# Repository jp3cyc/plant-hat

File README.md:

# plant-hat
ラズパイで植物の水やりをするための基板

# 機能
  - 12V入力対応（ラズパイ用USB電源不要）
  - 12VモータPWM駆動回路搭載
  - I2C用コネクタ搭載
  - ユニバーサル基板エリアあり
  - 3cm角ファン搭載可能

# 使い方
## 電源ON
  DCジャックに12V電源を差し込み，スイッチをONにするとラズパイが起動します．（Rev1基板ではON-OFFの印刷が逆転しています）
  
## GPIO操作
  - J7コネクタはGPIO 35，J6コネクタは32番に接続されています．
  - GPIO35番をONにしたいときは，GPIO35の出力をHにしてください．
  - GPIO35，GPIO32はPWM出力に対応しているので，PWM出力が可能です（未検証）
  - ラズパイのGPIOを操作できればソフトウェアは何でも使えます（例：C，Python，Node-redなど）

## 利用上の注意
Raspberry Piの時計のタイマーは符号付き32bit intで実装されている都合上，2038年1月19日12時14分7秒(JST)を超えると，1901年にタイムスリップします．
そのため，2038年1月19日12時14分7秒をまたぐ水やりを行うと，プログラムの実装によっては水が出続ける可能性があります．
ご利用時はご注意ください．

https://ja.wikipedia.org/wiki/2038%E5%B9%B4%E5%95%8F%E9%A1%8C
https://www.youtube.com/watch?v=WLyIPslm_rw

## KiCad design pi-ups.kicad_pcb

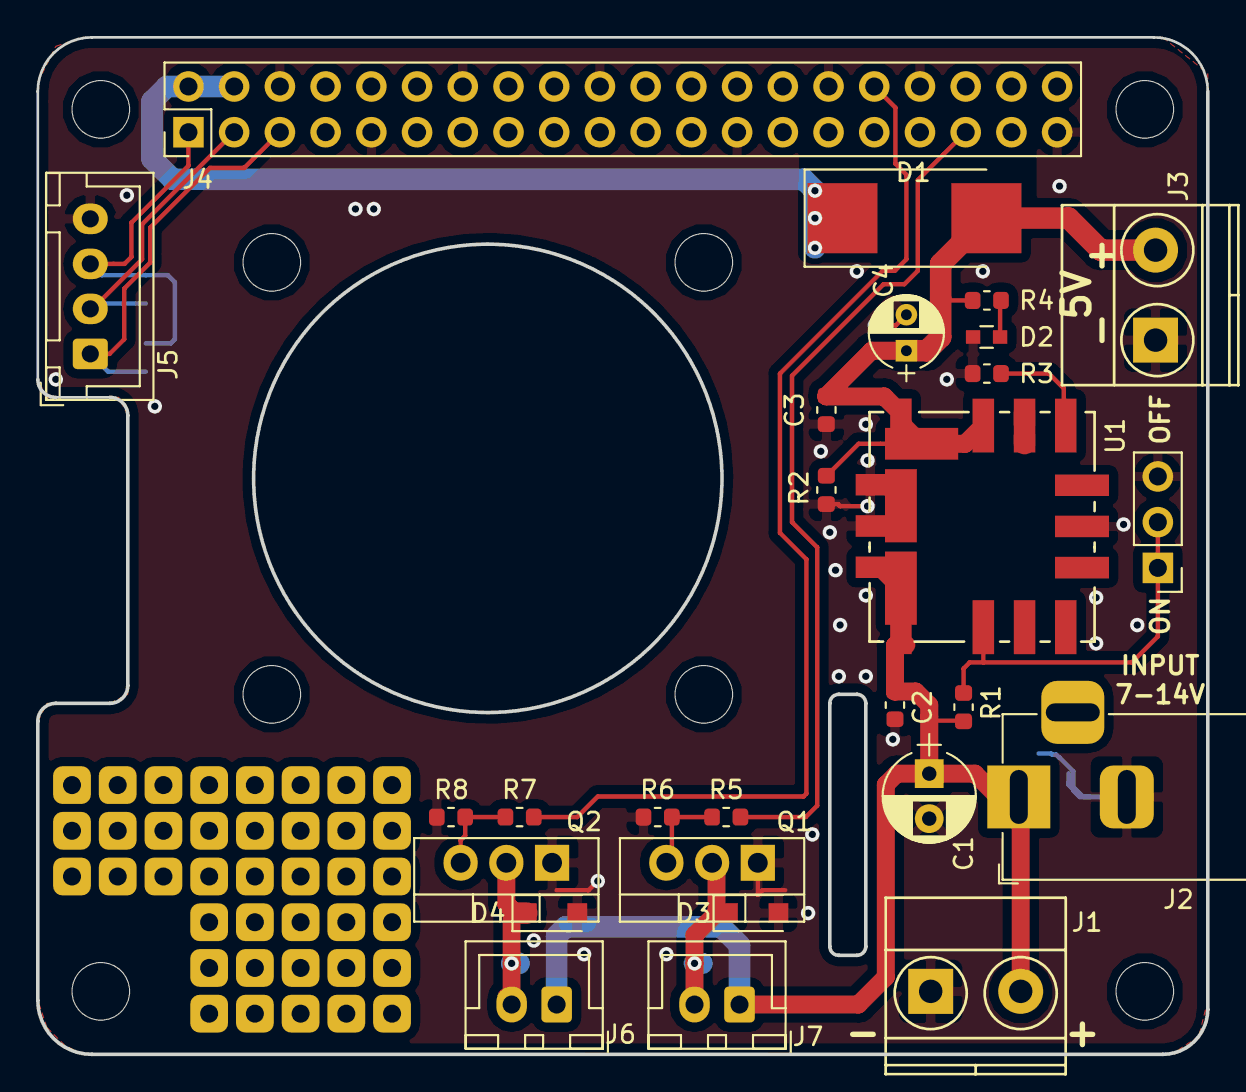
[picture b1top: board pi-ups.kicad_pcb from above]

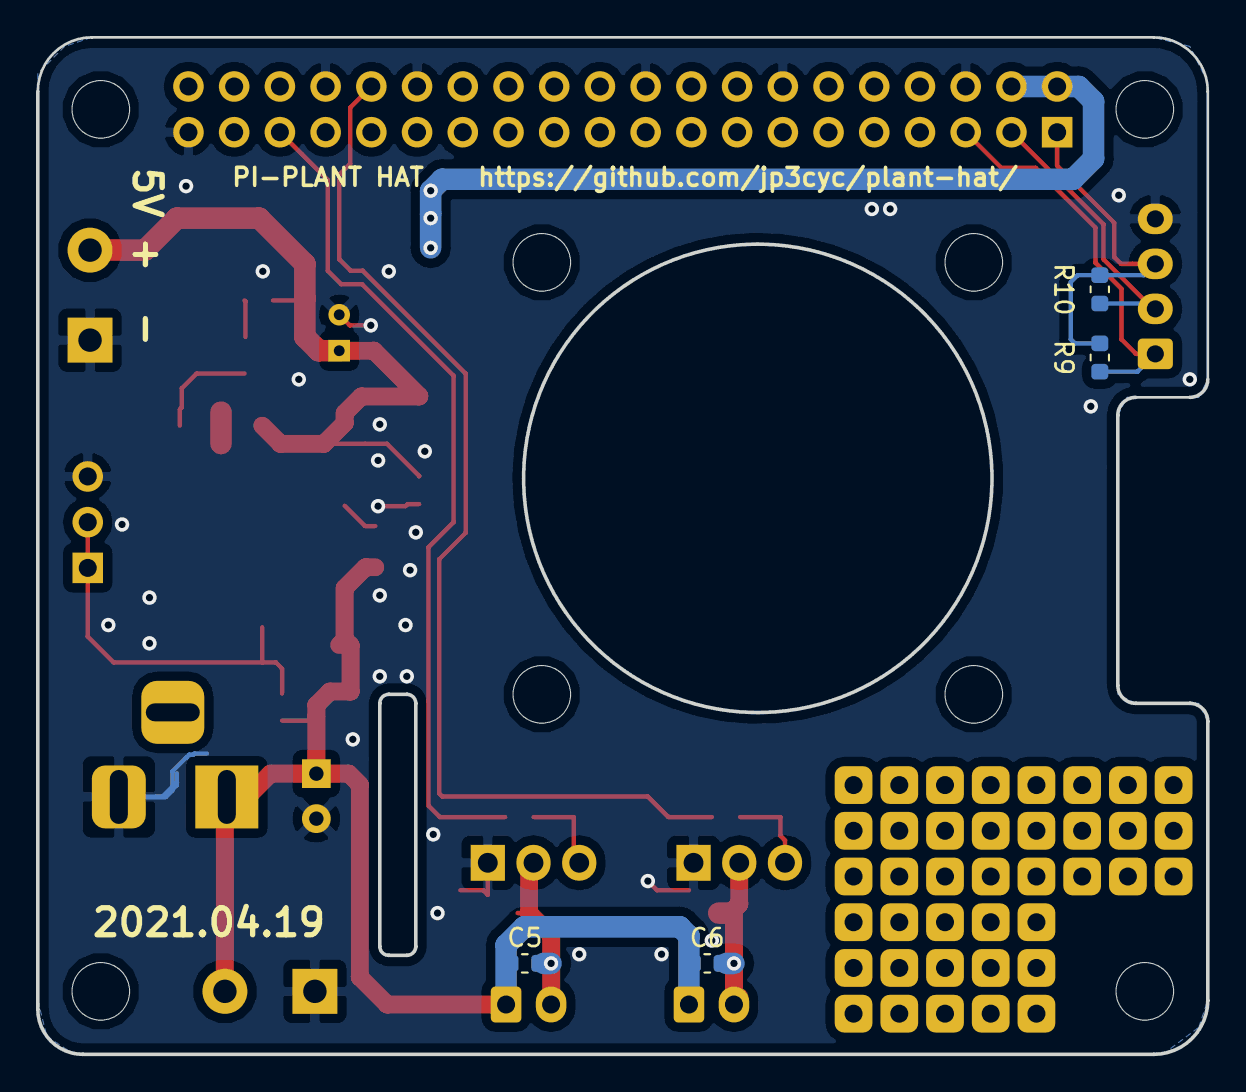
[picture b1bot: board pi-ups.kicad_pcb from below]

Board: 2 copper layers, 65.0 x 56.5 mm, 31 parts (4 on the bottom side), 16 nets.

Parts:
C1: 22u; CP_Radial_D5.0mm_P2.50mm
C2, C3, C5, C6: 0.1u; C_0603_1608Metric
C4: 10u; CP_Radial_D4.0mm_P2.00mm
D1: D; D_3220
D2: ON-LINE; C_0603
D3, D4: SS2040FL; D_SOD-123F
J1: Battery; TerminalBlock_Pheonix_MKDS1.5-2pol
J2: Jack-DC; BarrelJack_Horizontal
J3: 5V; TerminalBlock_Pheonix_MKDS1.5-2pol
J4: Raspi GPIO; Pin_Header_Straight_2x20_Pitch2.54mm
J5: I2C; JST_XH_B04B-XH-A_1x04_P2.50mm_Vertical
J6, J7: Motor; JST_XH_B02B-XH-A_1x02_P2.50mm_Vertical
Q1, Q2: 2SC4811; TO-220-3_Vertical
R1: 20k; R_0603_1608Metric
R2: 1.2k; R_0603_1608Metric
R3: 1.33k; R_0603_1608Metric
R4: 1k; R_0603_1608Metric
R5, R6, R7, R8: R; R_0603_1608Metric
R9, R10: 2.2k; R_0603_1608Metric
SW1: ON/OFF; Pin_Header_Straight_1x03_Pitch2.54mm
U1: OKL_T3_W12

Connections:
/5V: C3.1, C4.1, D1.2, J3.2, R2.1, R4.1, U1.4, U1.5
GND: C1.2, C2.1, C3.2, C4.2, D2.1, D3.2, D4.2, J1.1, J2.2, J3.1, J4.6, J4.9, J4.14, J4.20, J4.25, J4.30, J4.34, J4.39, J5.4, Q1.1, Q2.1, R2.2, R3.2, R6.2, R8.2, SW1.3, U1.3, U1.7
unnamed: C5.2, D3.1, J7.2, Q1.2
unnamed: C6.2, D4.1, J6.2, Q2.2
unnamed: D2.2, R4.2
unnamed: Q1.3, R5.1, R6.1
unnamed: Q2.3, R7.1, R8.1
unnamed: R1.2, SW1.1, SW1.2, U1.1
unnamed: R3.1, U1.6
Vin: C1.1, C2.2, C5.1, C6.1, J1.2, J2.1, J6.1, J7.1, R1.1, U1.2
pi-01: J4.1, J4.17, J5.3, R9.1, R10.1
pi-02: D1.1, J4.2, J4.4
pi-03: J4.3, J5.2, R10.2
pi-05: J4.5, J5.1, R9.2
pi-32: J4.32, R7.2
pi-35: J4.35, R5.2

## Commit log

2021-05-02 Init commit
2021-05-02 使い方を追加
2021-05-02 参考文献をついか
2021-08-11 organized data
2021-08-11 Fix readme.md
